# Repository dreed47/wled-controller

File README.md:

# WLED Controller (ESP32) - 4 Channels - Optional current and power monitoring

## Features

- 4 Channels
  - Max 25A total
  - Max 10A per channel
- Every channel has _independent_ current, power and voltage monitoring (using INA219)
- Sending power monitoring data to HomeAssistant via MQTT
- Seperate 3.3V low noise voltage regulator for audio section
- _**Optional:** INMP441 I2S Microphone with low noise power supply_
- Two versions of PCB esp32 dev kit and esp32 SMD
- This board requires a usermod for WLED for full support of all features including power monitoring.

## ESP32 Dev Kit Version

Interactive [BOM can be found here](https://rawcdn.githack.com/dreed47/wled-controller/main/bom/ibom.html).

### 3D Board view

### Board

## ESP32 SMD Version

Interactive [BOM can be found here](https://rawcdn.githack.com/dreed47/wled-controller/main/bom_smd/ibom.html).

### 3D Board view

### Board

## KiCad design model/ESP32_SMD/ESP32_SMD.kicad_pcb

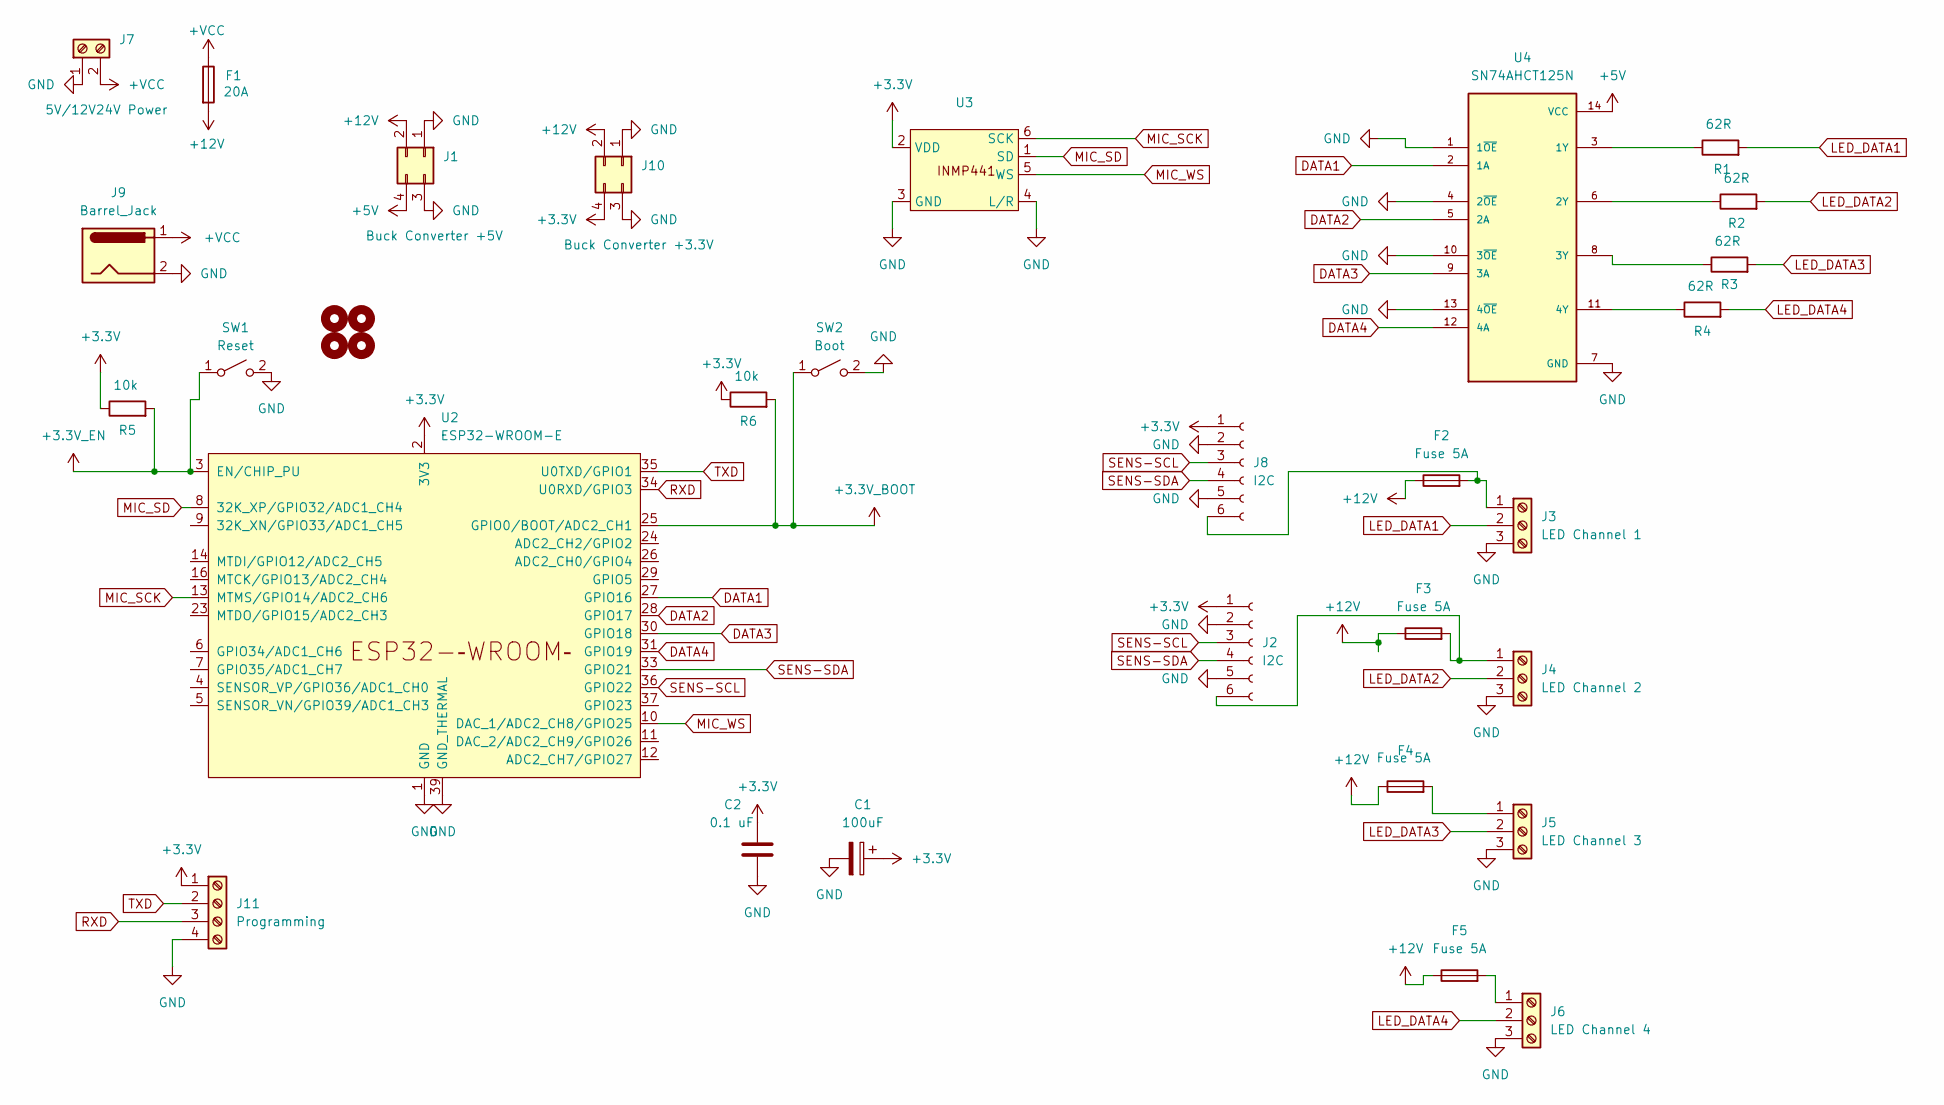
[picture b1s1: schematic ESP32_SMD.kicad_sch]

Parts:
C1: 100uF; CP_Radial_D10.0mm_P5.00mm
C2: 0.1 uF; C_Disc_D3.0mm_W1.6mm_P2.50mm
F1: 20A; Fuseholder_Blade_Mini_Keystone_3568
F2, F3, F4, F5: Fuse 5A; Fuse_Littelfuse-NANO2-451_453
H1, H2, H3, H4: MountingHole; MountingHole_2.2mm_M2_DIN965_Pad
J1: Buck Converter +5V; Buck Converter Board
J2, J8: I2C; PinHeader_1x06_P2.54mm_Vertical
J3: LED Channel 1; TerminalBlock_Phoenix_MPT-0,5-3-2.54_1x03_P2.54mm_Horizontal
J4: LED Channel 2; TerminalBlock_Phoenix_MPT-0,5-3-2.54_1x03_P2.54mm_Horizontal
J5: LED Channel 3; TerminalBlock_Phoenix_MPT-0,5-3-2.54_1x03_P2.54mm_Horizontal
J6: LED Channel 4; TerminalBlock_Phoenix_MPT-0,5-3-2.54_1x03_P2.54mm_Horizontal
J7: 5V/12V24V Power; PHOENIX_1935161
J9: Barrel_Jack; BarrelJack_Horizontal
J10: Buck Converter +3.3V; Buck Converter Board
J11: Programming; JST_XH_B4B-XH-A_1x04_P2.50mm_Vertical
R1, R2, R3, R4: 62R; R_Axial_DIN0207_L6.3mm_D2.5mm_P10.16mm_Horizontal
R5, R6: 10k; R_Axial_DIN0207_L6.3mm_D2.5mm_P10.16mm_Horizontal
SW1: Reset; SW_SPST_PTS647_Sx38
SW2: Boot; SW_SPST_PTS647_Sx38
U2: ESP32-WROOM-E; ESP32-WROOM-32E
U3: INMP441_Module
U4: SN74AHCT125N; DIP794W45P254L1930H508Q14; PARTREV Q; DigiKey_Part_Number 2156-SN74AHCT125N-ND

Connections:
+3.3V: C1.1, C2.1, J2.1, J8.1, J10.4, J11.1, R5.1, R6.1, U2.2 (3V3), U3.2 (VDD)
+3.3V_BOOT: R6.2, SW2.1 (A), U2.25 (GPIO0/BOOT/ADC2_CH1)
+3.3V_EN: R5.2, SW1.1 (A), U2.3 (EN/CHIP_PU)
+5V: J1.4, U4.14 (VCC)
+12V: F1.2, F2.1, F3.1, F4.1, F5.1, J1.2, J10.2
+VCC: F1.1, J7.2, J9.1
DATA1: U2.27 (GPIO16), U4.2 (1A)
DATA2: U2.28 (GPIO17), U4.5 (2A)
DATA3: U2.30 (GPIO18), U4.9 (3A)
DATA4: U2.31 (GPIO19), U4.12 (4A)
GND: C1.2, C2.2, J1.1, J1.3, J2.2, J2.5, J3.3, J4.3, J5.3, J6.3, J7.1, J8.2, J8.5, J9.2, J10.1, J10.3, J11.4, SW1.2 (B), SW2.2 (B), U2.1 (GND), U2.15 (GND), U2.38 (GND), U2.39 (GND_THERMAL), U3.3 (GND), U3.4 (L/R), U4.1 (1~OE), U4.4 (2~OE), U4.7 (GND), U4.10 (3~OE), U4.13 (4~OE)
LED_DATA1: J3.2, R1.2
LED_DATA2: J4.2, R2.2
LED_DATA3: J5.2, R3.2
LED_DATA4: J6.2, R4.2
MIC_SCK: U2.13 (MTMS/GPIO14/ADC2_CH6), U3.6 (SCK)
MIC_SD: U2.8 (32K_XP/GPIO32/ADC1_CH4), U3.1 (SD)
MIC_WS: U2.10 (DAC_1/ADC2_CH8/GPIO25), U3.5 (WS)
unnamed: F3.2, J2.6, J4.1
unnamed: F2.2, J3.1, J8.6
unnamed: F4.2, J5.1
unnamed: F5.2, J6.1
unnamed: R1.1, U4.3 (1Y)
unnamed: R2.1, U4.6 (2Y)
unnamed: R3.1, U4.8 (3Y)
unnamed: R4.1, U4.11 (4Y)
RXD: J11.3, U2.34 (U0RXD/GPIO3)
SENS-SCL: J2.3, J8.3, U2.36 (GPIO22)
SENS-SDA: J2.4, J8.4, U2.33 (GPIO21)
TXD: J11.2, U2.35 (U0TXD/GPIO1)

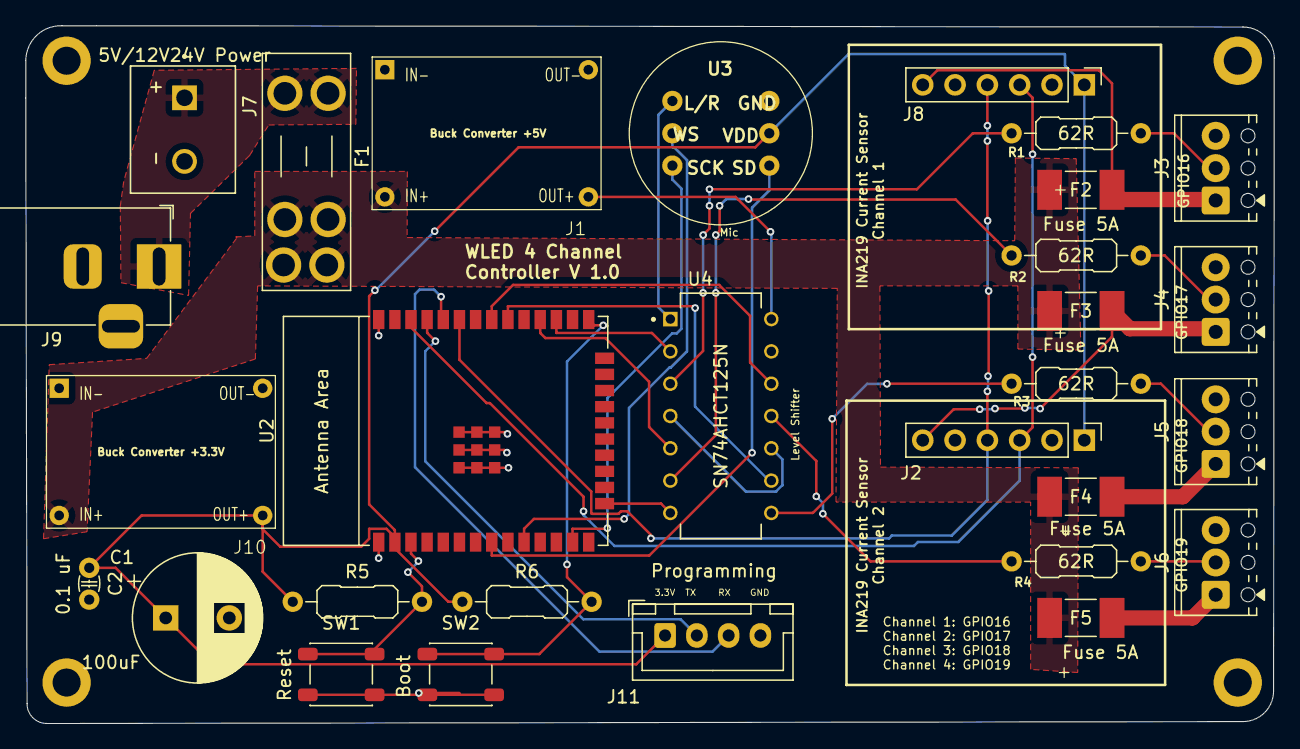
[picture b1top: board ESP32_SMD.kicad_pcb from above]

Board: 2 copper layers, 98.2 x 54.9 mm, 33 parts (0 on the bottom side), 30 nets.

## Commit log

2025-03-09 fixed barrel jack
2025-03-09 fix barrell jack
